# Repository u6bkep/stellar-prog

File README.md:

# stellar-prog

A programmer for Hanshow Stellar-L3N e-ink shelf tags (2.9" black/white/red, Telink TLSR8359,
512 KB flash), and a web page that drives it: back up a tag's stock flash and put custom BLE
firmware on it from the browser, with nothing to install.

| | |
|---|---|
| `pcb/stellar_prog/` | The fixture: a single-sided board with a Waveshare RP2350-Zero and eight pogo pins that land on the tag's programming pads inside the battery compartment |
| `firmware/` | pico-sws, the firmware for the RP2350-Zero (also builds for a hand-wired RP2040 Pico): a Telink SWire master and a tag UART, over USB serial |
| `webui/` | The static web page (Web Serial; WebUSB only to update the programmer) |
| `docs/protocol.md` | The USB protocol between the page and the programmer |
| `scripts/` | UF2 packaging, and fetching/building the third-party tag firmware |

## Using it

Open the published page in a Chromium-based desktop browser, plug in the fixture, and follow the
page: connect, detect the tag, back up, flash. Flashing the BLE firmware overwrites the Hanshow
bootloader, so the backup the page makes you download is the only way back to stock.

A new RP2350-Zero has no firmware: hold BOOT while plugging it in, then use the page's "update
programmer" step, or drag `pico-sws.uf2` from the latest release onto the drive that appears.

## Building

    # programmer firmware (see firmware/README.md)
    (cd firmware && cargo build --release --target thumbv6m-none-eabi)
    (cd firmware && cargo build --release --target thumbv8m.main-none-eabihf --no-default-features --features rp2350)
    scripts/make-uf2.sh dist-fw                # needs picotool

    # floader + tag BLE firmware, from their pinned upstream commits, hash-checked
    scripts/fetch-tag-firmware.sh dist-tag

    # the site
    webui/build.sh --programmer dist-fw --tag-firmware dist-tag --version dev
    python3 -m http.server -d webui/dist 8000  # http://localhost:8000

`webui/build.sh` with no arguments builds a page without bundled firmware; it then works with
files you pick. Tests for the page's protocol and flashing logic run against a simulated
programmer and tag: `node --test --test-concurrency=1 "webui/test/*.test.js"`.

Pushing a `v*` tag runs `.github/workflows/release.yml`: it builds everything above, attaches the
programmer UF2s to a GitHub release, and deploys the page to GitHub Pages (repo setting: Pages
source "GitHub Actions").

## Credits

This project's own work is the fixture, the programmer firmware and the page. The parts that run
on the tag are other people's, fetched at build time and not stored in this repository:

- **floader**, the flash loader that runs from the tag's RAM: pvvx,
  [TlsrComProg825x](https://github.com/pvvx/TlsrComProg825x).
- **The BLE firmware**: atc1441's [ATC_TLSR_Paper](https://github.com/atc1441/ATC_TLSR_Paper),
  in reece15's port to this tag, [stellar-L3N-etag](https://github.com/reece15/stellar-L3N-etag).

The activation sequence (reset while sending CPU-stop) is also pvvx's.

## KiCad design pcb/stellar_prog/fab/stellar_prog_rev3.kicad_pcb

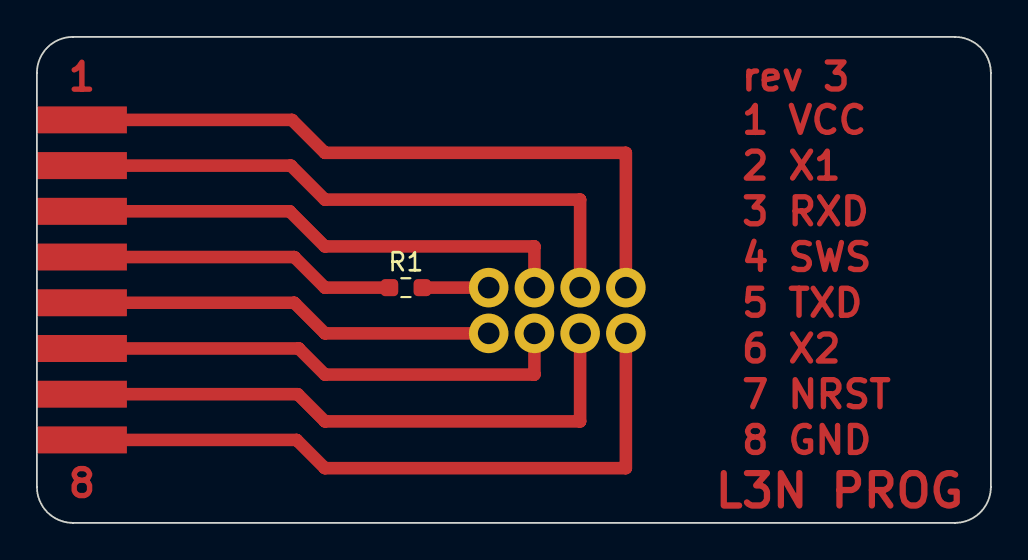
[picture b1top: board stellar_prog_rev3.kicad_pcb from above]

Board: 2 copper layers, 53.0 x 27.0 mm, 3 parts (0 on the bottom side), 9 nets.

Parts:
J1: hdr_1x8_flat
P1: L3N_pogo_2x4
R1: 1k; R_0603_1608Metric_Pad0.98x0.95mm_HandSolder

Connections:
GND: J1.8, P1.8
NRST: J1.7, P1.7
RXD: J1.3, P1.2
SWS: J1.4, R1.1
SWS_TAG: P1.1, R1.2
TXD: J1.5, P1.5
VCC: J1.1, P1.4
X1: J1.2, P1.3
X2: J1.6, P1.6

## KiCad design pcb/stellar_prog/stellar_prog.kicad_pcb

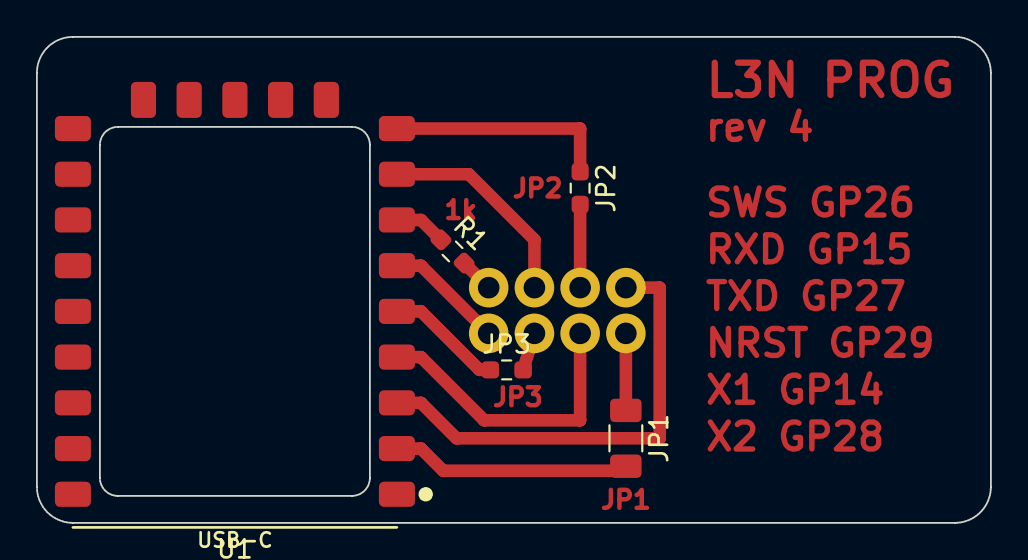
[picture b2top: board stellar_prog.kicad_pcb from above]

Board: 2 copper layers, 53.0 x 27.0 mm, 6 parts (0 on the bottom side), 12 nets.

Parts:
JP1: 0R; R_1206_3216Metric_Pad1.30x1.75mm_HandSolder
JP2, JP3: DNP; R_0603_1608Metric_Pad0.98x0.95mm_HandSolder
P1: L3N_pogo_2x4
R1: 1k; R_0603_1608Metric_Pad0.98x0.95mm_HandSolder
U1: RP2350-Zero

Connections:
GND: JP1.2, U1.GND
GND_TAG: JP1.1, P1.8
NRST: P1.7, U1.GP29
RXD: P1.2, U1.GP15
SWS: R1.1, U1.GP26
SWS_TAG: P1.1, R1.2
TXD: P1.5, U1.GP27
VCC: P1.4, U1.3V3
X1: JP2.2, P1.3
X1_GP: JP2.1, U1.GP14
X2: JP3.2, P1.6
X2_GP: JP3.1, U1.GP28
